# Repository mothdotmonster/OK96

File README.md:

# WARNING!!! this design has not been tested. it probably doesn't work and you should not use it as a reference.

# OK96
96-key ortho keyboard with through-hole components

This work is licensed under a
[Creative Commons Attribution-ShareAlike 4.0 International License][cc-by-sa].

[![CC BY-SA 4.0][cc-by-sa-image]][cc-by-sa]

[cc-by-sa]: http://creativecommons.org/licenses/by-sa/4.0/
[cc-by-sa-image]: https://licensebuttons.net/l/by-sa/4.0/88x31.png

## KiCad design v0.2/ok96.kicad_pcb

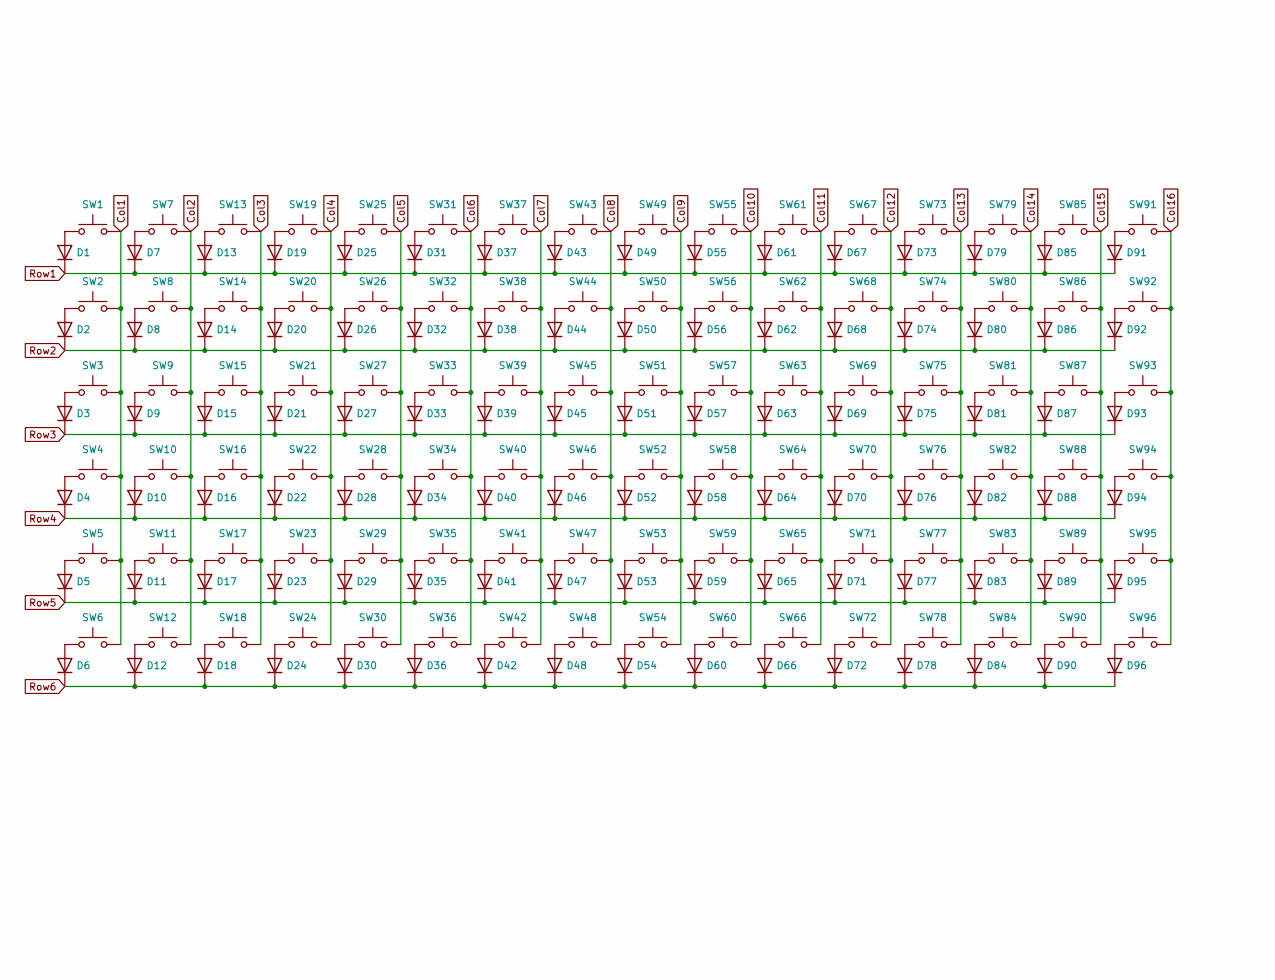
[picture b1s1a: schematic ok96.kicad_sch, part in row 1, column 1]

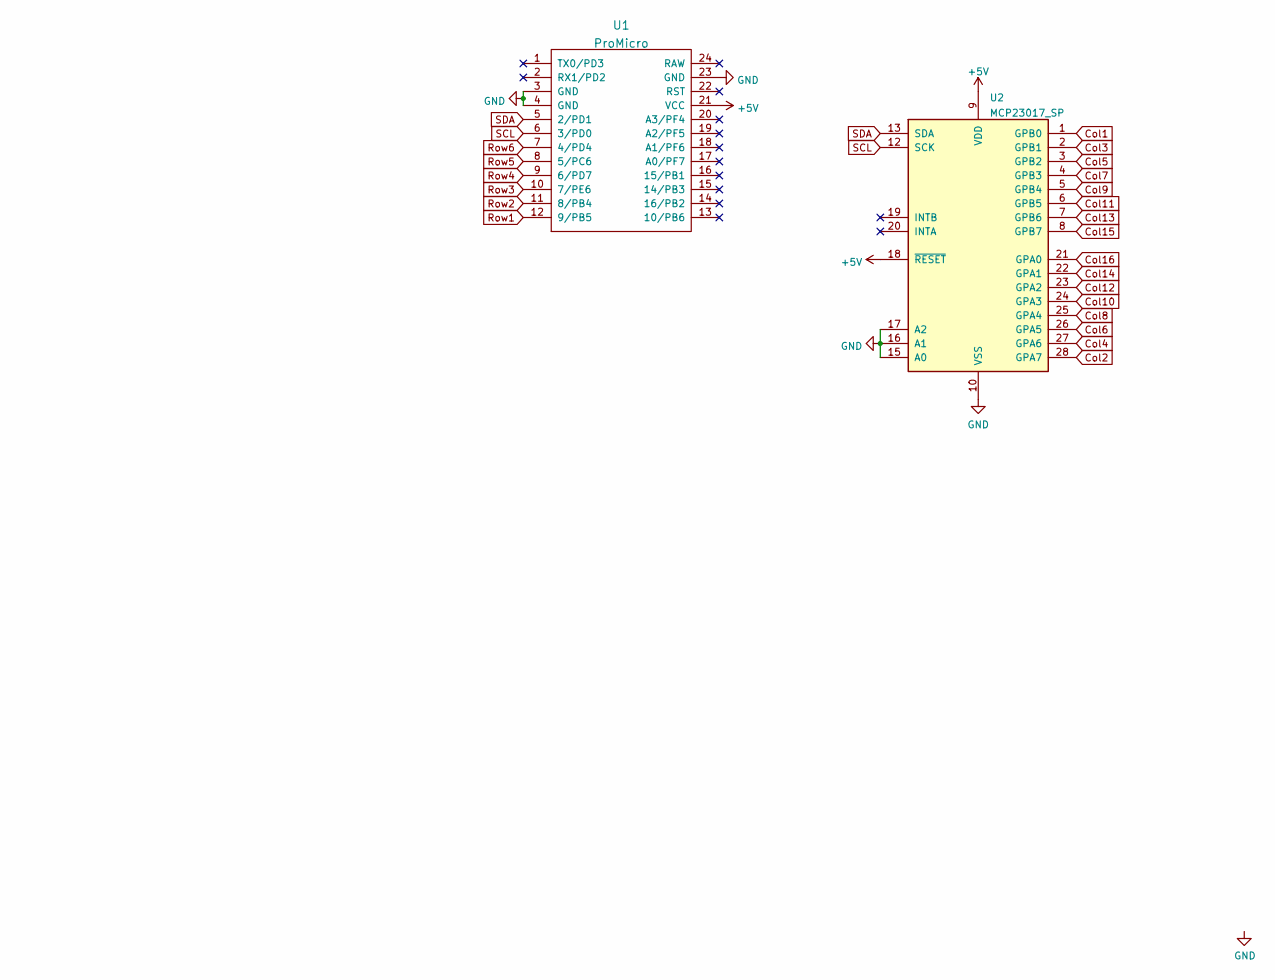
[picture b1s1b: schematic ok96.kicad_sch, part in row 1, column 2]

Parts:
D1, D2, D3, D4, D5, D6, D7, D8, D9, D10, D11, D12, D13, D14, D15, D16, D17, D18, D19, D20, D21, D22, D23, D24, D25, D26, D27, D28, D29, D30, D31, D32, D33, D34, D35, D36, D37, D38, D39, D40, D41, D42, D43, D44, D45, D46, D47, D48, D49, D50, D51, D52, D53, D54, D55, D56, D57, D58, D59, D60, D61, D62, D63, D64, D65, D66, D67, D68, D69, D70, D71, D72, D73, D74, D75, D76, D77, D78, D79, D80, D81, D82, D83, D84, D85, D86, D87, D88, D89, D90, D91, D92, D93, D94, D95, D96: D; D_DO-34_SOD68_P7.62mm_Horizontal
SW1, SW2, SW3, SW4, SW5, SW6, SW7, SW8, SW9, SW10, SW11, SW12, SW13, SW14, SW15, SW16, SW17, SW18, SW19, SW20, SW21, SW22, SW23, SW24, SW25, SW26, SW27, SW28, SW29, SW30, SW31, SW32, SW33, SW34, SW35, SW36, SW37, SW38, SW39, SW40, SW41, SW42, SW43, SW44, SW45, SW46, SW47, SW48, SW49, SW50, SW51, SW52, SW53, SW54, SW55, SW56, SW57, SW58, SW59, SW60, SW61, SW62, SW63, SW64, SW65, SW66, SW67, SW68, SW69, SW70, SW71, SW72, SW73, SW74, SW75, SW76, SW77, SW78, SW79, SW80, SW81, SW82, SW83, SW84, SW85, SW86, SW87, SW88, SW89, SW90, SW91, SW92, SW93, SW94, SW95, SW96: SW_Push; SW_Cherry_MX_1.00u_PCB
U1: ProMicro; ArduinoProMicro
U2: MCP23017_SP; DIP-28_W7.62mm

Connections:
+5V: U1.21 (VCC), U2.9 (VDD), U2.18 (~RESET)
Col1: SW1.2, SW2.2, SW3.2, SW4.2, SW5.2, SW6.2, U2.1 (GPB0)
Col2: SW7.2, SW8.2, SW9.2, SW10.2, SW11.2, SW12.2, U2.28 (GPA7)
Col3: SW13.2, SW14.2, SW15.2, SW16.2, SW17.2, SW18.2, U2.2 (GPB1)
Col4: SW19.2, SW20.2, SW21.2, SW22.2, SW23.2, SW24.2, U2.27 (GPA6)
Col5: SW25.2, SW26.2, SW27.2, SW28.2, SW29.2, SW30.2, U2.3 (GPB2)
Col6: SW31.2, SW32.2, SW33.2, SW34.2, SW35.2, SW36.2, U2.26 (GPA5)
Col7: SW37.2, SW38.2, SW39.2, SW40.2, SW41.2, SW42.2, U2.4 (GPB3)
Col8: SW43.2, SW44.2, SW45.2, SW46.2, SW47.2, SW48.2, U2.25 (GPA4)
Col9: SW49.2, SW50.2, SW51.2, SW52.2, SW53.2, SW54.2, U2.5 (GPB4)
Col10: SW55.2, SW56.2, SW57.2, SW58.2, SW59.2, SW60.2, U2.24 (GPA3)
Col11: SW61.2, SW62.2, SW63.2, SW64.2, SW65.2, SW66.2, U2.6 (GPB5)
Col12: SW67.2, SW68.2, SW69.2, SW70.2, SW71.2, SW72.2, U2.23 (GPA2)
Col13: SW73.2, SW74.2, SW75.2, SW76.2, SW77.2, SW78.2, U2.7 (GPB6)
Col14: SW79.2, SW80.2, SW81.2, SW82.2, SW83.2, SW84.2, U2.22 (GPA1)
Col15: SW85.2, SW86.2, SW87.2, SW88.2, SW89.2, SW90.2, U2.8 (GPB7)
Col16: SW91.2, SW92.2, SW93.2, SW94.2, SW95.2, SW96.2, U2.21 (GPA0)
GND: U1.3 (GND), U1.4 (GND), U1.23 (GND), U2.10 (VSS), U2.15 (A0), U2.16 (A1), U2.17 (A2)
unnamed: D1.2 (A), SW1.1
unnamed: D2.2 (A), SW2.1
unnamed: D3.2 (A), SW3.1
unnamed: D4.2 (A), SW4.1
unnamed: D5.2 (A), SW5.1
unnamed: D6.2 (A), SW6.1
unnamed: D7.2 (A), SW7.1
unnamed: D8.2 (A), SW8.1
unnamed: D9.2 (A), SW9.1
unnamed: D10.2 (A), SW10.1
unnamed: D11.2 (A), SW11.1
unnamed: D12.2 (A), SW12.1
unnamed: D13.2 (A), SW13.1
unnamed: D14.2 (A), SW14.1
unnamed: D15.2 (A), SW15.1
unnamed: D16.2 (A), SW16.1
unnamed: D17.2 (A), SW17.1
unnamed: D18.2 (A), SW18.1
unnamed: D19.2 (A), SW19.1
unnamed: D20.2 (A), SW20.1
unnamed: D21.2 (A), SW21.1
unnamed: D22.2 (A), SW22.1
unnamed: D23.2 (A), SW23.1
unnamed: D24.2 (A), SW24.1
unnamed: D25.2 (A), SW25.1
unnamed: D26.2 (A), SW26.1
unnamed: D27.2 (A), SW27.1
unnamed: D28.2 (A), SW28.1
unnamed: D29.2 (A), SW29.1
unnamed: D30.2 (A), SW30.1
unnamed: D31.2 (A), SW31.1
unnamed: D32.2 (A), SW32.1
unnamed: D33.2 (A), SW33.1
unnamed: D34.2 (A), SW34.1
unnamed: D35.2 (A), SW35.1
unnamed: D36.2 (A), SW36.1
unnamed: D37.2 (A), SW37.1
unnamed: D38.2 (A), SW38.1
unnamed: D39.2 (A), SW39.1
unnamed: D40.2 (A), SW40.1
unnamed: D41.2 (A), SW41.1
unnamed: D42.2 (A), SW42.1
unnamed: D43.2 (A), SW43.1
unnamed: D44.2 (A), SW44.1
unnamed: D45.2 (A), SW45.1
unnamed: D46.2 (A), SW46.1
unnamed: D47.2 (A), SW47.1
unnamed: D48.2 (A), SW48.1
unnamed: D49.2 (A), SW49.1
unnamed: D50.2 (A), SW50.1
unnamed: D51.2 (A), SW51.1
unnamed: D52.2 (A), SW52.1
unnamed: D53.2 (A), SW53.1
unnamed: D54.2 (A), SW54.1
unnamed: D55.2 (A), SW55.1
unnamed: D56.2 (A), SW56.1
unnamed: D57.2 (A), SW57.1
unnamed: D58.2 (A), SW58.1
unnamed: D59.2 (A), SW59.1
unnamed: D60.2 (A), SW60.1
unnamed: D61.2 (A), SW61.1
unnamed: D62.2 (A), SW62.1
unnamed: D63.2 (A), SW63.1
unnamed: D64.2 (A), SW64.1
unnamed: D65.2 (A), SW65.1
unnamed: D66.2 (A), SW66.1
unnamed: D67.2 (A), SW67.1
unnamed: D68.2 (A), SW68.1
unnamed: D69.2 (A), SW69.1
unnamed: D70.2 (A), SW70.1
unnamed: D71.2 (A), SW71.1
unnamed: D72.2 (A), SW72.1
unnamed: D73.2 (A), SW73.1
unnamed: D74.2 (A), SW74.1
unnamed: D75.2 (A), SW75.1
unnamed: D76.2 (A), SW76.1
unnamed: D77.2 (A), SW77.1
unnamed: D78.2 (A), SW78.1
unnamed: D79.2 (A), SW79.1
unnamed: D80.2 (A), SW80.1
unnamed: D81.2 (A), SW81.1
unnamed: D82.2 (A), SW82.1
unnamed: D83.2 (A), SW83.1
unnamed: D84.2 (A), SW84.1
unnamed: D85.2 (A), SW85.1
unnamed: D86.2 (A), SW86.1
unnamed: D87.2 (A), SW87.1
unnamed: D88.2 (A), SW88.1
unnamed: D89.2 (A), SW89.1
unnamed: D90.2 (A), SW90.1
unnamed: D91.2 (A), SW91.1
unnamed: D92.2 (A), SW92.1
unnamed: D93.2 (A), SW93.1
unnamed: D94.2 (A), SW94.1
unnamed: D95.2 (A), SW95.1
unnamed: D96.2 (A), SW96.1
Row1: D1.1 (K), D7.1 (K), D13.1 (K), D19.1 (K), D25.1 (K), D31.1 (K), D37.1 (K), D43.1 (K), D49.1 (K), D55.1 (K), D61.1 (K), D67.1 (K), D73.1 (K), D79.1 (K), D85.1 (K), D91.1 (K), U1.12 (9/PB5)
Row2: D2.1 (K), D8.1 (K), D14.1 (K), D20.1 (K), D26.1 (K), D32.1 (K), D38.1 (K), D44.1 (K), D50.1 (K), D56.1 (K), D62.1 (K), D68.1 (K), D74.1 (K), D80.1 (K), D86.1 (K), D92.1 (K), U1.11 (8/PB4)
Row3: D3.1 (K), D9.1 (K), D15.1 (K), D21.1 (K), D27.1 (K), D33.1 (K), D39.1 (K), D45.1 (K), D51.1 (K), D57.1 (K), D63.1 (K), D69.1 (K), D75.1 (K), D81.1 (K), D87.1 (K), D93.1 (K), U1.10 (7/PE6)
Row4: D4.1 (K), D10.1 (K), D16.1 (K), D22.1 (K), D28.1 (K), D34.1 (K), D40.1 (K), D46.1 (K), D52.1 (K), D58.1 (K), D64.1 (K), D70.1 (K), D76.1 (K), D82.1 (K), D88.1 (K), D94.1 (K), U1.9 (6/PD7)
Row5: D5.1 (K), D11.1 (K), D17.1 (K), D23.1 (K), D29.1 (K), D35.1 (K), D41.1 (K), D47.1 (K), D53.1 (K), D59.1 (K), D65.1 (K), D71.1 (K), D77.1 (K), D83.1 (K), D89.1 (K), D95.1 (K), U1.8 (5/PC6)
Row6: D6.1 (K), D12.1 (K), D18.1 (K), D24.1 (K), D30.1 (K), D36.1 (K), D42.1 (K), D48.1 (K), D54.1 (K), D60.1 (K), D66.1 (K), D72.1 (K), D78.1 (K), D84.1 (K), D90.1 (K), D96.1 (K), U1.7 (4/PD4)
SCL: U1.6 (3/PD0), U2.12 (SCK)
SDA: U1.5 (2/PD1), U2.13 (SDA)

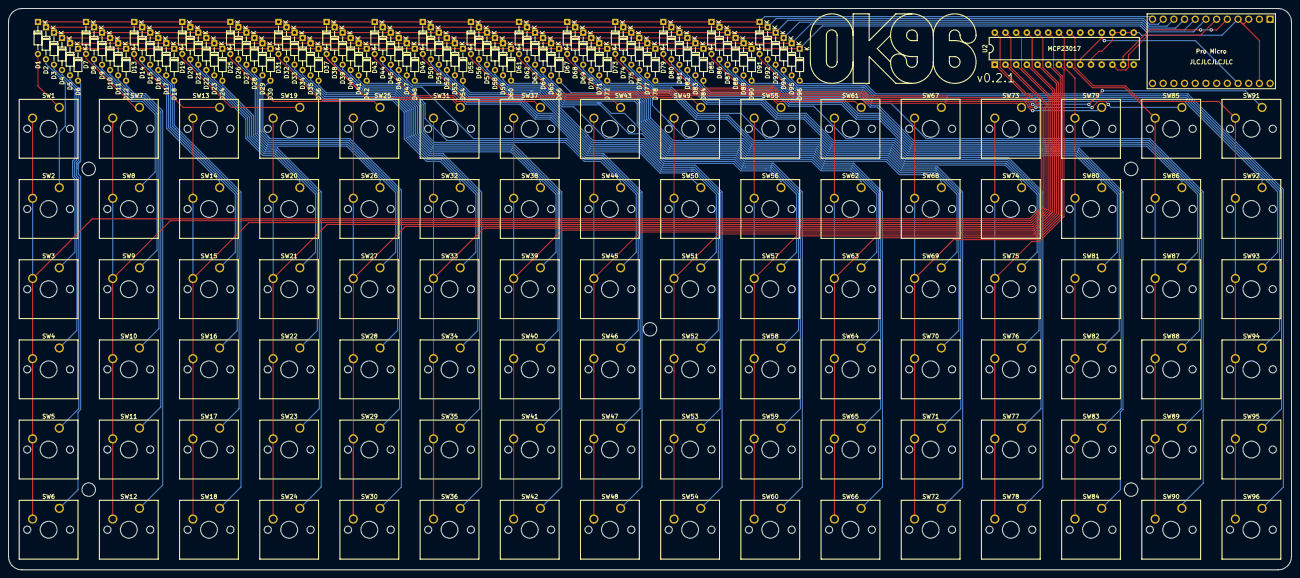
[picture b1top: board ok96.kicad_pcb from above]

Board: 2 copper layers, 304.8 x 133.3 mm, 194 parts (0 on the bottom side), 122 nets.

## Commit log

2021-05-10 v0.1 upload
2021-05-10 minor silkscreen fixes, v0.1.1
2021-05-10 Add license
2022-02-08 new design
    uses a pro micro and io expander instead of trying to do everything from scratch
